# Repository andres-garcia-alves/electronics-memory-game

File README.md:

# Memory-Game

Arduino code for a 4 coloured memory game (Simon) 

&nbsp;

This project use the following electronic components:
- 1 x Arduino Nano v3
- 1 x Display 5621AS-1, 7-segments, 2-digit, common catode
- 4 x LEDs (red, blue, yellow & green)
- 1 x Buzzer
- 5 x Push-button
- 8 x 470 ohm resistors
- 4 x 330 ohm resistors
- 1 x Batery 9v

Notes:
- Edit `Definitions.h` to adjust configured display pins to your own display model.

&nbsp;

### Screenshots

| Schematic Diagram                              | PBC Layout                                     |
|------------------------------------------------|------------------------------------------------|
|      |             |

| PCB 3D Render                                  | PBC 3D Render                                  |
|------------------------------------------------|------------------------------------------------|
|          |          |

| Prototype                                      | Building                                       |
|------------------------------------------------|------------------------------------------------|
|              |               |

| Building                                       | Building (Finished)                            |
|------------------------------------------------|------------------------------------------------|
|               |      |

| Building (Finished)                            | Box Shaping                                    |
|------------------------------------------------|------------------------------------------------|
|      |               |

| Project Final                                  | Project Final (YouTube video)                  |
|------------------------------------------------|------------------------------------------------|
|          |  |

See 'Rescources' sub-folder for more pictures & videos of the project.

&nbsp;

### Version History

v1.0 (2023.03.08) - Initial release.  
v1.1 (2023.03.09) - Refactor for mudularity (adding concept of micro-commands for user inteccions).  
v1.2 (2023.03.10) - Improved animations.  
v1.3 (2023.03.15) - Pinout rearrange for easy soldering.  
v1.4 (2023.03.18) - Adding game finished sequence.  
v1.5 (2025.12.20) - Update project structure.  
v1.6 (2025.12.26) - Adding KiCAD 9 schematics and PCB diagrams.  

&nbsp;

This source code is licensed under GPL v3.0  
Please send me your feedback about this project: andres.garcia.alves@gmail.com

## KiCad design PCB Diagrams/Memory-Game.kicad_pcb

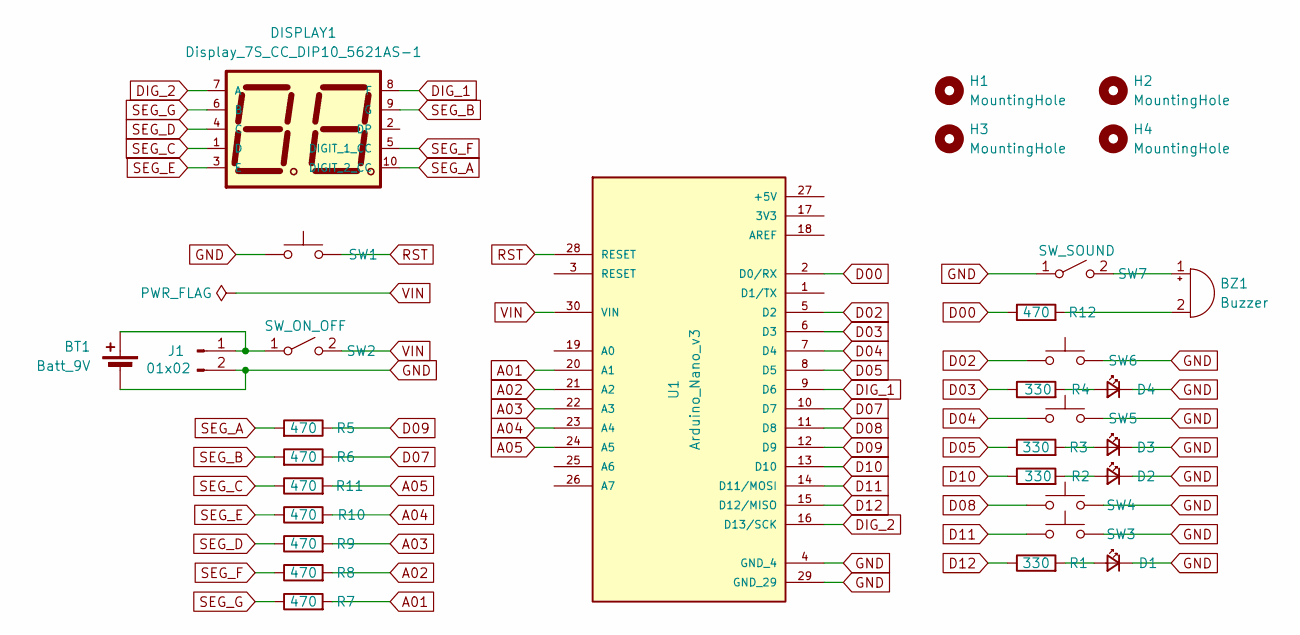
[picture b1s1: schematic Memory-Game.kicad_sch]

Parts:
BT1: Batt_9V; BatteryHolder_Eagle_12BH611-GR
BZ1: Buzzer; Buzzer_12x9.5RM7.6
D1, D2, D3, D4: LED; LED_D5.0mm
DISPLAY1: Display_7S_CC_DIP10_5621AS-1; Display_7S_CC_DIP10_VCC_C565S9
H1, H2, H3, H4: MountingHole; MountingHole_2mm
J1: 01x02; R_Axial_DIN0204_L3.6mm_D1.6mm_P2.54mm_Vertical
R1, R2, R3, R4: 330; R_Axial_DIN0204_L3.6mm_D1.6mm_P2.54mm_Vertical
R5, R6, R7, R8, R9, R10, R11, R12: 470; R_Axial_DIN0204_L3.6mm_D1.6mm_P2.54mm_Vertical
SW1, SW3, SW4, SW5, SW6: SW_Push; SW_PUSH_6mm_H9.5mm
SW2: SW_ON_OFF; SW_DIP_SPSTx01_Slide_9.78x4.72mm_W7.62mm_P2.54mm
SW7: SW_SOUND; SW_DIP_SPSTx01_Slide_9.78x4.72mm_W7.62mm_P2.54mm
U1: Arduino_Nano_v3

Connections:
A01: R7.2, U1.20 (A1)
A02: R8.2, U1.21 (A2)
A03: R9.2, U1.22 (A3)
A04: R10.2, U1.23 (A4)
A05: R11.2, U1.24 (A5)
D00: R12.1, U1.2 (D0/RX)
D02: SW6.1, U1.5 (D2)
D03: R4.1, U1.6 (D3)
D04: SW5.1, U1.7 (D4)
D05: R3.1, U1.8 (D5)
D07: R6.1, U1.10 (D7)
D08: SW4.1, U1.11 (D8)
D09: R5.1, U1.12 (D9)
D10: R2.1, U1.13 (D10)
D11: SW3.1, U1.14 (D11/MOSI)
D12: R1.1, U1.15 (D12/MISO)
DIG_1: DISPLAY1.8 (F), U1.9 (D6)
DIG_2: DISPLAY1.7 (A), U1.16 (D13/SCK)
GND: BT1.2 (-), D1.1 (K), D2.1 (K), D3.1 (K), D4.1 (K), J1.2, SW1.1, SW3.2, SW4.2, SW5.2, SW6.2, SW7.1 (A), U1.4 (GND_4), U1.29 (GND_29)
unnamed: BT1.1 (+), J1.1, SW2.1 (A)
unnamed: BZ1.1 (+), SW7.2 (B)
unnamed: BZ1.2 (-), R12.2
unnamed: D1.2 (A), R1.2
unnamed: D2.2 (A), R2.2
unnamed: D3.2 (A), R3.2
unnamed: D4.2 (A), R4.2
RST: SW1.2, U1.28 (RESET)
SEG_A: DISPLAY1.10 (DIGIT_2_CC), R5.2
SEG_B: DISPLAY1.9 (G), R6.2
SEG_C: DISPLAY1.1 (D), R11.1
SEG_D: DISPLAY1.4 (C), R9.1
SEG_E: DISPLAY1.3 (E), R10.1
SEG_F: DISPLAY1.5 (DIGIT_1_CC), R8.1
SEG_G: DISPLAY1.6 (B), R7.1
VIN: SW2.2 (B), U1.30 (VIN)

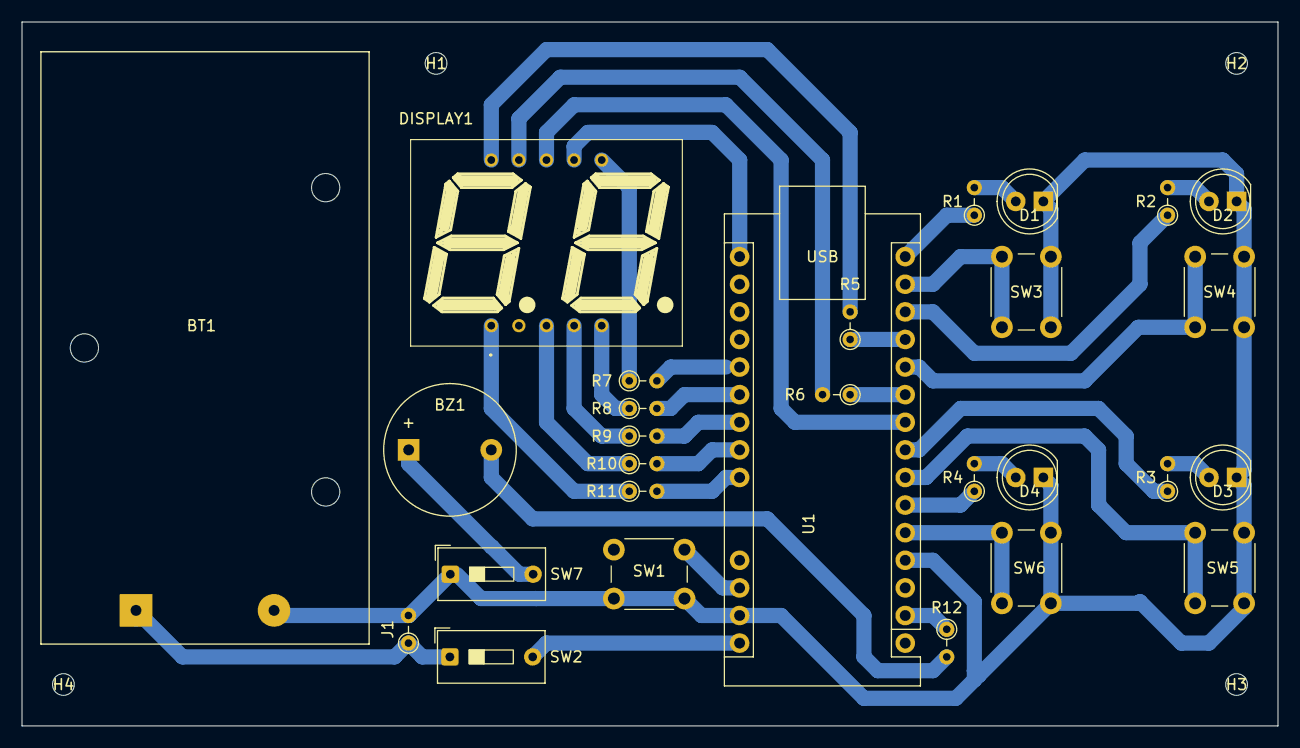
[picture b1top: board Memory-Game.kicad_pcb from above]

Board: 2 copper layers, 115.6 x 64.8 mm, 32 parts (0 on the bottom side), 35 nets.

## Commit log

2025-12-20 update project structure
2025-12-26 Adding KiCAD 9 schematics and PCB diagrams
